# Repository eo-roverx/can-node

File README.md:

# CAN Node PCB Designs

Part of the new arm system, wherein each PCB drives one motor, provides it feedback control, and (if needed) gives back IMU and encoder data. Our CAN node will have the following features:

- CAN bus communication
- IMU (accelerometer, gyroscope)
- Motor encoder input
- Motor driver
- 4 user defined LEDs + one status LED
- 4 bit address DIP switch
- ESP32 microcontroller: integration and feedback control

## Components
- ESP32 Microcontroller
- ESP32 power capacitor
- MPU9250 IMU
- MCP2551 CAN Transceiver
- 2x CAN RJ45 ports
- 2x XT60 solder pads for power
- MD13 Motor Driver
- MD13 power XT60 solder pads
- MD13 signal JST
- motor encoder JST
- 5V buck converter
- 2x 4.7k ohms I2C pull-up resistors
- CAN termination resistor solder pads
- I2C debug solder pads
- CAN Rx-Tx debug solder pads
- 4x dip switch
- 4x 10k ohm pull-down resistors
- 1 power LED
- 1 status LED
- 4 user defined LEDs
    - 2 used for CRx-CTx
    - 1 used for MPU calibration
    - 1 used for sync
- 6x 2k ohm current limiting resistors

## ESP32 Pin-out

### CAN Bus
-  D2 CAN Rx
- D15 CAN Tx

### IMU
- D21 SDA
- D22 SCL
- D18 FSYNC
- D19 INT

### Motor encoder
- D34 pin A
- D33 pin B

### MD13 Motor Driver
- D26 PWM
- D25 DIR

### LEDs
- D32 status
- D13 user 0 (Sync: all nodes are connected)
- D12 user 1 (CAN Rx)
- D14 user 2 (CAN Tx)
- D27 user 3 (MPU calibration)

### Address DIP switches
- D4 address 0
- RX2 address 1
- TX2 address 2
- D5 address 3

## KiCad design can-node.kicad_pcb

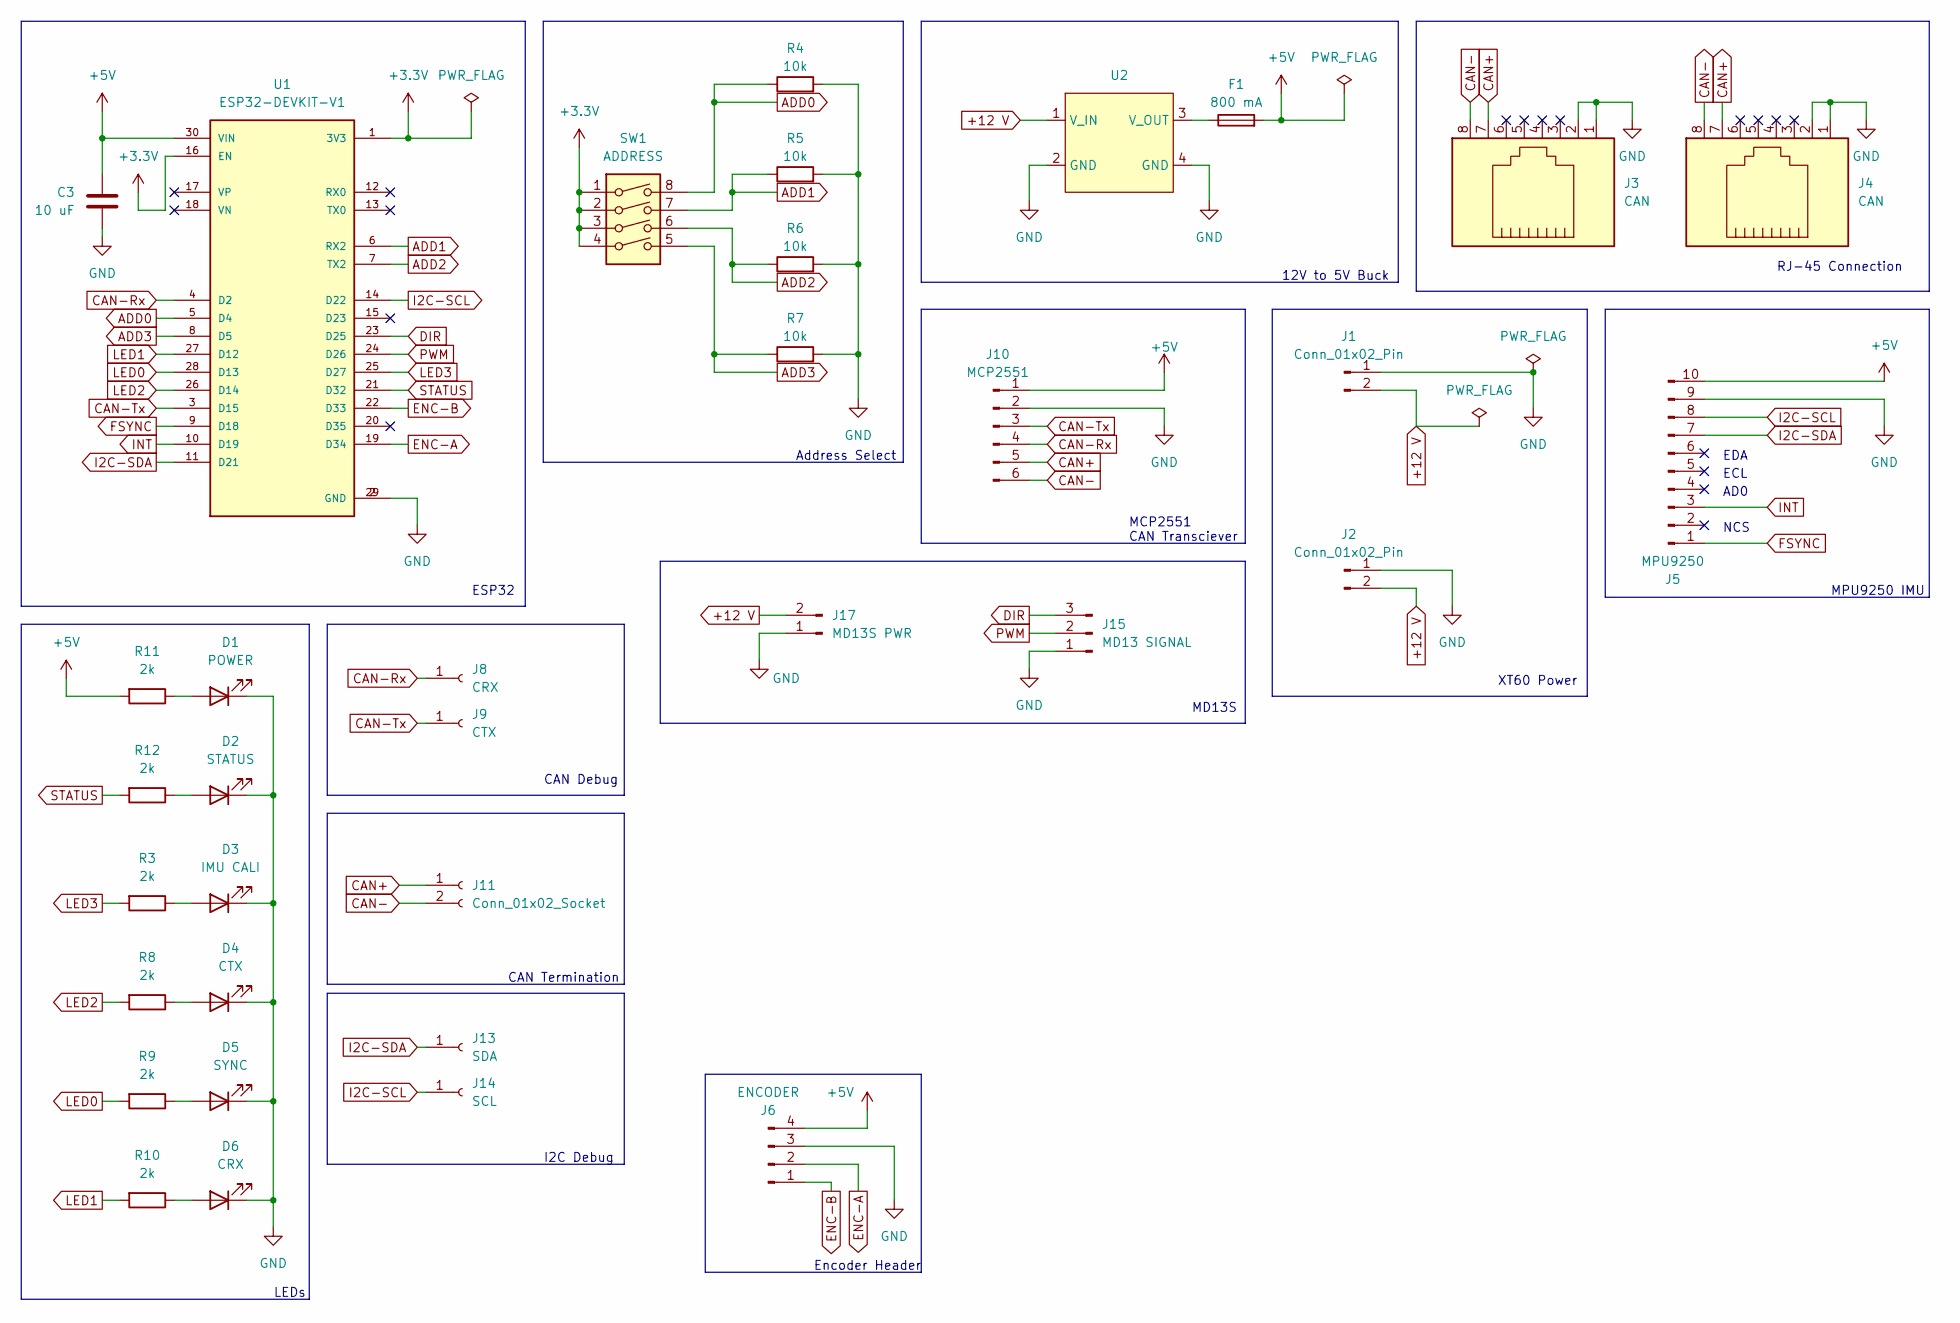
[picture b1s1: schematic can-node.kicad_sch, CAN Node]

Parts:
C3: 10 uF; C_0805_2012Metric
D1: POWER; LED_D3.0mm
D2: STATUS; LED_D3.0mm
D3: IMU CALI; LED_D3.0mm
D4: CTX; LED_D3.0mm
D5: SYNC; LED_D3.0mm
D6: CRX; LED_D3.0mm
F1: 800 mA; Fuse_0805_2012Metric_Pad1.15x1.40mm_HandSolder
J1, J2: Conn_01x02_Pin; SolderWire-1.5sqmm_1x02_P7.8mm_D1.7mm_OD3.9mm
J3, J4: CAN; RJ45_Amphenol_54602-x08_Horizontal
J5: MPU9250; PinHeader_1x10_P2.54mm_Vertical
J6: ENCODER; JST_PH_B4B-PH-K_1x04_P2.00mm_Vertical
J8: CRX; SolderWire-0.1sqmm_1x01_D0.4mm_OD1mm
J9: CTX; SolderWire-0.1sqmm_1x01_D0.4mm_OD1mm
J10: MCP2551; PinHeader_1x06_P2.54mm_Vertical
J11: Conn_01x02_Socket; SolderWire-0.1sqmm_1x02_P3.6mm_D0.4mm_OD1mm
J13: SDA; SolderWire-0.1sqmm_1x01_D0.4mm_OD1mm
J14: SCL; SolderWire-0.1sqmm_1x01_D0.4mm_OD1mm
J15: MD13 SIGNAL; JST_PH_S3B-PH-K_1x03_P2.00mm_Horizontal
J17: MD13S PWR; SolderWire-1sqmm_1x02_P7.8mm_D1.4mm_OD3.9mm
R3, R8, R9, R10, R11, R12: 2k; R_Axial_DIN0204_L3.6mm_D1.6mm_P5.08mm_Horizontal
R4, R5, R6, R7: 10k; R_Axial_DIN0204_L3.6mm_D1.6mm_P5.08mm_Horizontal
SW1: ADDRESS; SW_DIP_SPSTx04_Slide_6.7x11.72mm_W7.62mm_P2.54mm_LowProfile
U1: ESP32-DEVKIT-V1; MODULE_ESP32_DEVKIT_V1; PARTREV N/A
U2: MINI_360_Buck

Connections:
+3.3V: SW1.1, SW1.2, SW1.3, SW1.4, U1.1 (3V3), U1.16 (EN)
+5V: C3.1, F1.2, J5.10, J6.4, J10.1, R11.2, U1.30 (VIN)
+12 V: J1.2, J2.2, J17.2, U2.1 (V_IN)
ADD0: R4.1, SW1.8, U1.5 (D4)
ADD1: R5.1, SW1.7, U1.6 (RX2)
ADD2: R6.1, SW1.6, U1.7 (TX2)
ADD3: R7.1, SW1.5, U1.8 (D5)
CAN+: J3.7, J4.7, J10.5, J11.1
CAN-: J3.8, J4.8, J10.6, J11.2
CAN-Rx: J8.1, J10.4, U1.4 (D2)
CAN-Tx: J9.1, J10.3, U1.3 (D15)
DIR: J15.3, U1.23 (D25)
ENC-A: J6.2, U1.19 (D34)
ENC-B: J6.1, U1.22 (D33)
FSYNC: J5.1, U1.9 (D18)
GND: C3.2, D1.1 (K), D2.1 (K), D3.1 (K), D4.1 (K), D5.1 (K), D6.1 (K), J1.1, J2.1, J3.1, J3.2, J4.1, J4.2, J5.9, J6.3, J10.2, J15.1, J17.1, R4.2, R5.2, R6.2, R7.2, U1.2 (GND), U1.29 (GND), U2.2 (GND), U2.4 (GND)
I2C-SCL: J5.8, J14.1, U1.14 (D22)
I2C-SDA: J5.7, J13.1, U1.11 (D21)
INT: J5.3, U1.10 (D19)
LED0: R9.2, U1.28 (D13)
LED1: R10.2, U1.27 (D12)
LED2: R8.2, U1.26 (D14)
LED3: R3.2, U1.25 (D27)
unnamed: D1.2 (A), R11.1
unnamed: D2.2 (A), R12.1
unnamed: D3.2 (A), R3.1
unnamed: D4.2 (A), R8.1
unnamed: D5.2 (A), R9.1
unnamed: D6.2 (A), R10.1
unnamed: F1.1, U2.3 (V_OUT)
PWM: J15.2, U1.24 (D26)
STATUS: R12.2, U1.21 (D32)

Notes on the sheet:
ESP32
12V to 5V Buck
NCS
RJ-45 Connection
Address Select
MCP2551 CAN Transciever
CAN Termination
I2C Debug
ECL
XT60 Power
MPU9250 IMU
MD13S
LEDs
Encoder Header
AD0
CAN Debug
EDA

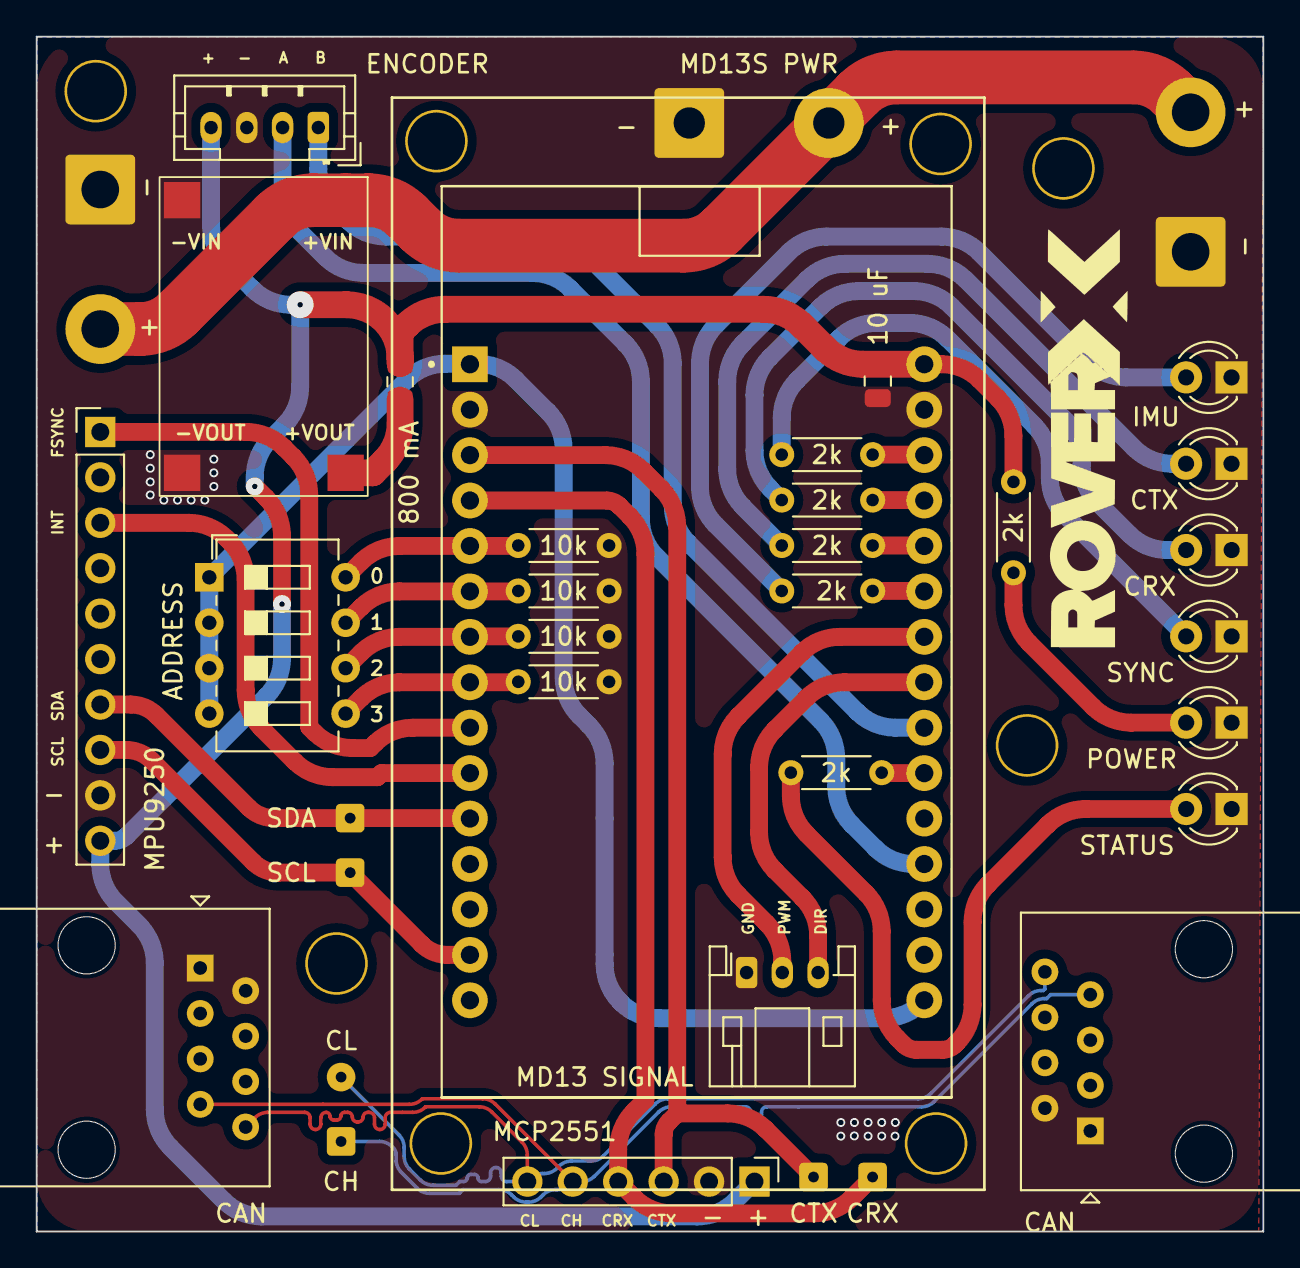
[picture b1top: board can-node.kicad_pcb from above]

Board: 2 copper layers, 68.6 x 66.8 mm, 35 parts (0 on the bottom side), 32 nets.

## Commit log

2023-11-03 v1 for esp32 breakout
2023-11-04 placed PCB components
2023-11-04 additional labelling
2023-11-06 draft?
2023-11-06 first try
2023-11-07 3D-ified
2023-11-07 fixed footprints
2023-11-07 routing attempt
2023-11-07 update for 3D
2023-11-09 update with feedback
2023-11-10 diff pair and mount holes
2023-11-10 add vias
2023-11-12 debug 5V trace
2023-11-20 add silkscreen
2023-11-22 add readme
2023-11-24 add CAN Rx & CAN Tx LEDs
2023-11-24 assign pins for other LEDs
2023-11-24 finish reroute
2023-11-24 smol silkscreen bug :)
2023-11-24 readme
2023-11-25 silkscreen update
2023-11-25 forgot small power components
2023-11-25 add esp32 usb to sk, ignore gerbers
2023-11-28 fix 5V for MCP
2023-12-01 add 5V
2023-12-01 clean up silkscreen
2023-12-07 rm i2c pull-ups
2023-12-31 add pinout
